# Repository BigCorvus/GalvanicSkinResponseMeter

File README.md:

# GalvanicSkinResponseMeter
Measures changes in skin conductance, outputs analog voltage. Based on the "Truth Meter" by Makezine.

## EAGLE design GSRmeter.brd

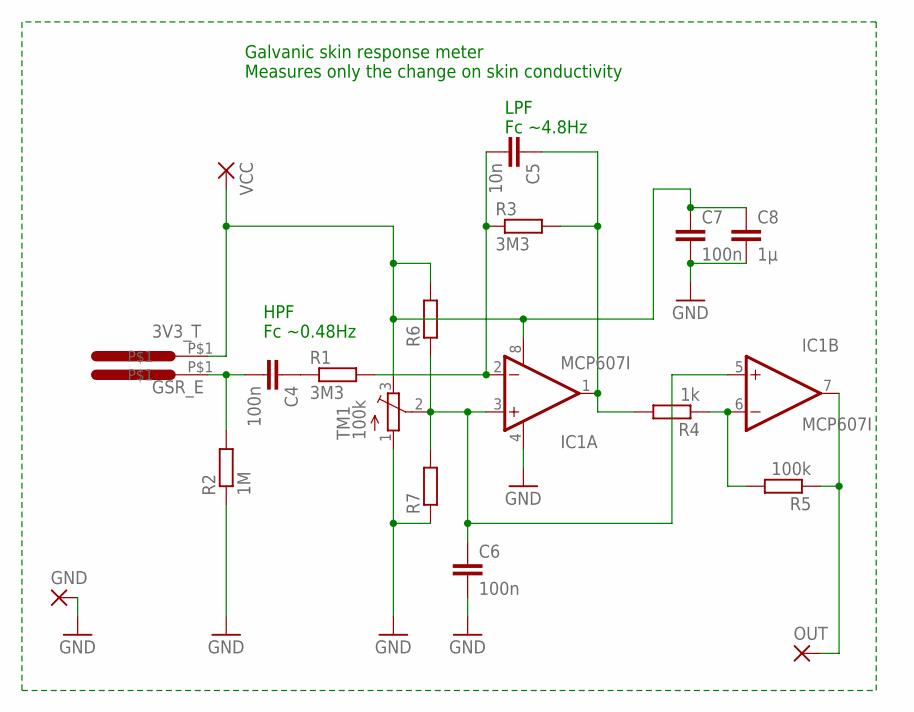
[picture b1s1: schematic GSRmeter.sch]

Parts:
C4, C6, C7: 100n; C0603K
C5: 10n; C0603K
C8: 1µ; C0603K
GND: SMD5; SMD2,54-5,08
IC1: MCP607I; SO08
OUT: SMD5; SMD2,54-5,08
R1, R3: 3M3; R0603
R2: 1M; R0603
R4: 1k; R0603
R5: 100k; R0603
R6, R7: R-EU_R0402; R0402
TM1: 100k; TC33X
U$1, U$2: ELECTRODE
VCC: SMD5; SMD2,54-5,08

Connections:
3V3_T: C7.1, C8.1, IC1.8 (V+), R6.2, TM1.3 (E), U$1.P$1, VCC.1
GND: C6.2, C7.2, C8.2, GND.1, IC1.4 (V-), R2.1, R7.1, TM1.1 (A)
GSR_E: C4.2, R2.2, U$2.P$1
unnamed: C5.2, IC1.2 (-IN), R1.2, R3.1
unnamed: C5.1, IC1.1 (OUT), R3.2, R4.2
unnamed: C6.1, IC1.3 (+IN), IC1.5 (+IN), R6.1, R7.2, TM1.2 (S)
unnamed: C4.1, R1.1
unnamed: IC1.6 (-IN), R4.1, R5.2
unnamed: IC1.7 (OUT), OUT.1, R5.1

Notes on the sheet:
Galvanic skin response meter Measures only the change on skin conductivity
HPF Fc ~0.48Hz
LPF Fc ~4.8Hz

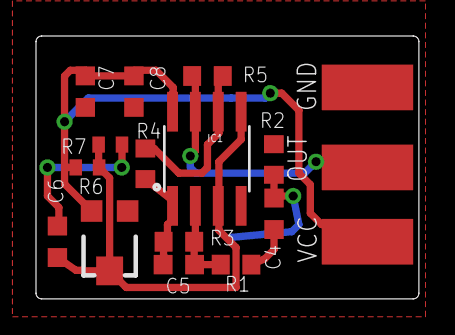
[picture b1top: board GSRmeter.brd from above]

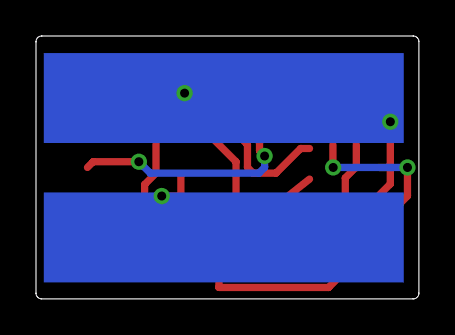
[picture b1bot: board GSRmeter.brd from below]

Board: 2 copper layers, 21.3 x 14.6 mm, 19 parts (2 on the bottom side), 9 nets.

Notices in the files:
parts and their libraries:
SparkFun-AnalogIC: Licensing:Creative Commons ShareAlike 4.0 International - https://creativecommons.org/licenses/by-sa/4.0
